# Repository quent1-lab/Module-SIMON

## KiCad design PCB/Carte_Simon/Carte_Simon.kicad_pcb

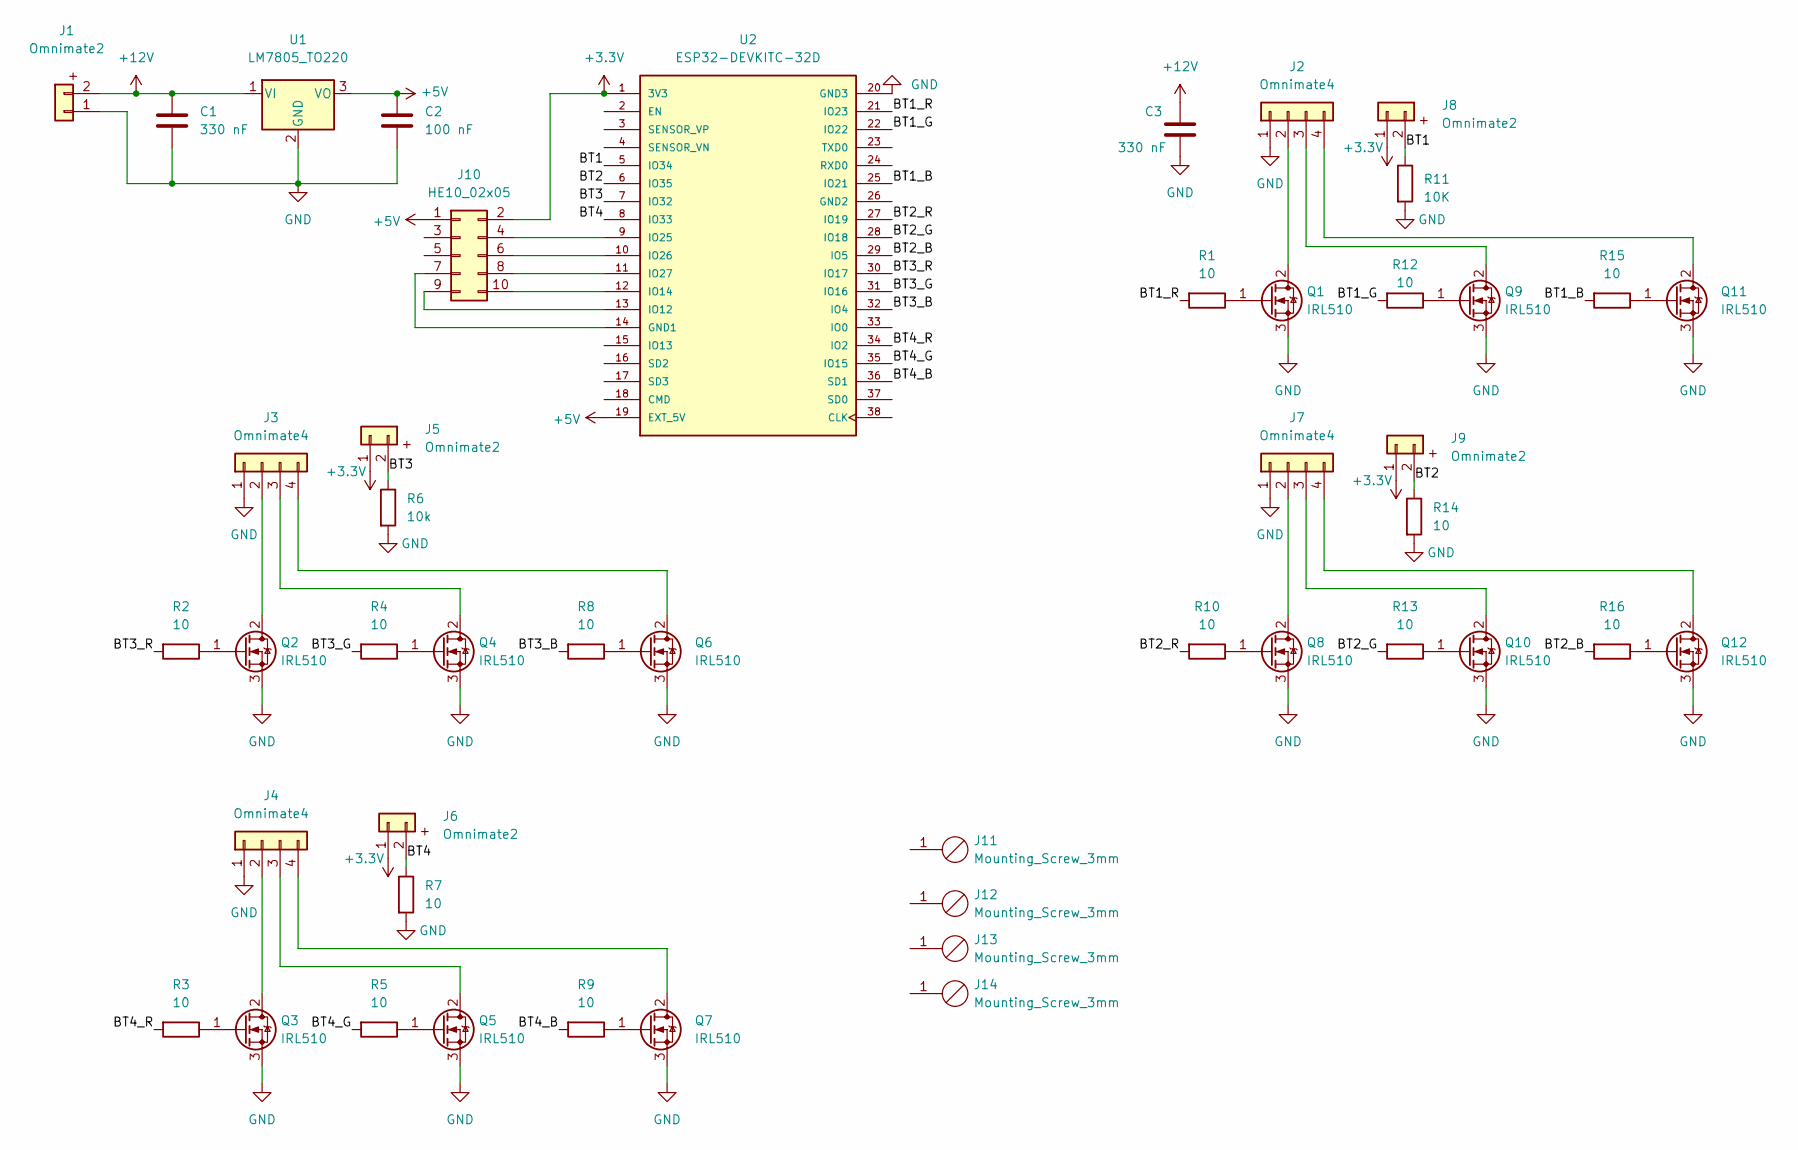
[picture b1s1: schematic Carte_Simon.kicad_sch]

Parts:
C1, C3: 330 nF; C_Rect_L7.0mm_W2.5mm_P5.00mm
C2: 100 nF; C_Rect_L7.0mm_W2.5mm_P5.00mm
J1, J5, J6, J8, J9: Omnimate2; OmnimateSL-5,08_1x02_P5.08mm_Vertical
J2, J3, J4, J7: Omnimate4; OmnimateSL-5,08_1x04_P5.08mm_Vertical
J10: HE10_02x05; HE10_2x05_P2.54mm
J11, J12, J13, J14: Mounting_Screw_3mm
Q1, Q2, Q3, Q4, Q5, Q6, Q7, Q8, Q9, Q10, Q11, Q12: IRL510; TO-220-3_Vertical
R1, R2, R3, R4, R5, R7, R8, R9, R10, R12, R13, R14, R15, R16: 10; R_Axial_DIN0207_L6.3mm_D2.5mm_P10.16mm_Horizontal
R6: 10k; R_Axial_DIN0207_L6.3mm_D2.5mm_P10.16mm_Horizontal
R11: 10K; R_Axial_DIN0207_L6.3mm_D2.5mm_P10.16mm_Horizontal
U1: LM7805_TO220; TO-220-3_Vertical
U2: ESP32-DEVKITC-32D; MODULE_ESP32-DEVKITC-32D; PARTREV 4

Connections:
+3.3V: J5.1, J6.1, J8.1, J9.1, J10.2, U2.1 (3V3)
+5V: C2.1, J10.1, U1.3 (VO), U2.19 (EXT_5V)
+12V: C1.1, C3.1, J1.2, U1.1 (VI)
/BT1: J8.2, R11.1, U2.5 (IO34)
/BT1_B: R15.2, U2.25 (IO21)
/BT1_G: R12.2, U2.22 (IO22)
/BT1_R: R1.2, U2.21 (IO23)
/BT2: J9.2, R14.1, U2.6 (IO35)
/BT2_B: R16.2, U2.29 (IO5)
/BT2_G: R13.2, U2.28 (IO18)
/BT2_R: R10.2, U2.27 (IO19)
/BT3: J5.2, R6.1, U2.7 (IO32)
/BT3_B: R8.2, U2.32 (IO4)
/BT3_G: R4.2, U2.31 (IO16)
/BT3_R: R2.2, U2.30 (IO17)
/BT4: J6.2, R7.1, U2.8 (IO33)
/BT4_B: R9.2, U2.36 (SD1)
/BT4_G: R5.2, U2.35 (IO15)
/BT4_R: R3.2, U2.34 (IO2)
GND: C1.2, C2.2, C3.2, J1.1, J2.1, J3.1, J4.1, J7.1, Q1.3 (S), Q2.3 (S), Q3.3 (S), Q4.3 (S), Q5.3 (S), Q6.3 (S), Q7.3 (S), Q8.3 (S), Q9.3 (S), Q10.3 (S), Q11.3 (S), Q12.3 (S), R6.2, R7.2, R11.2, R14.2, U1.2 (GND), U2.20 (GND3)
unnamed: J2.2, Q1.2 (D)
unnamed: J2.3, Q9.2 (D)
unnamed: J2.4, Q11.2 (D)
unnamed: J3.2, Q2.2 (D)
unnamed: J3.3, Q4.2 (D)
unnamed: J3.4, Q6.2 (D)
unnamed: J4.2, Q3.2 (D)
unnamed: J4.3, Q5.2 (D)
unnamed: J4.4, Q7.2 (D)
unnamed: J7.2, Q8.2 (D)
unnamed: J7.3, Q10.2 (D)
unnamed: J7.4, Q12.2 (D)
unnamed: J10.4, U2.9 (IO25)
unnamed: J10.6, U2.10 (IO26)
unnamed: J10.7, U2.14 (GND1)
unnamed: J10.8, U2.11 (IO27)
unnamed: J10.9, U2.13 (IO12)
unnamed: J10.10, U2.12 (IO14)
unnamed: Q1.1 (G), R1.1
unnamed: Q2.1 (G), R2.1
unnamed: Q3.1 (G), R3.1
unnamed: Q4.1 (G), R4.1
unnamed: Q5.1 (G), R5.1
unnamed: Q6.1 (G), R8.1
unnamed: Q7.1 (G), R9.1
unnamed: Q8.1 (G), R10.1
unnamed: Q9.1 (G), R12.1
unnamed: Q10.1 (G), R13.1
unnamed: Q11.1 (G), R15.1
unnamed: Q12.1 (G), R16.1

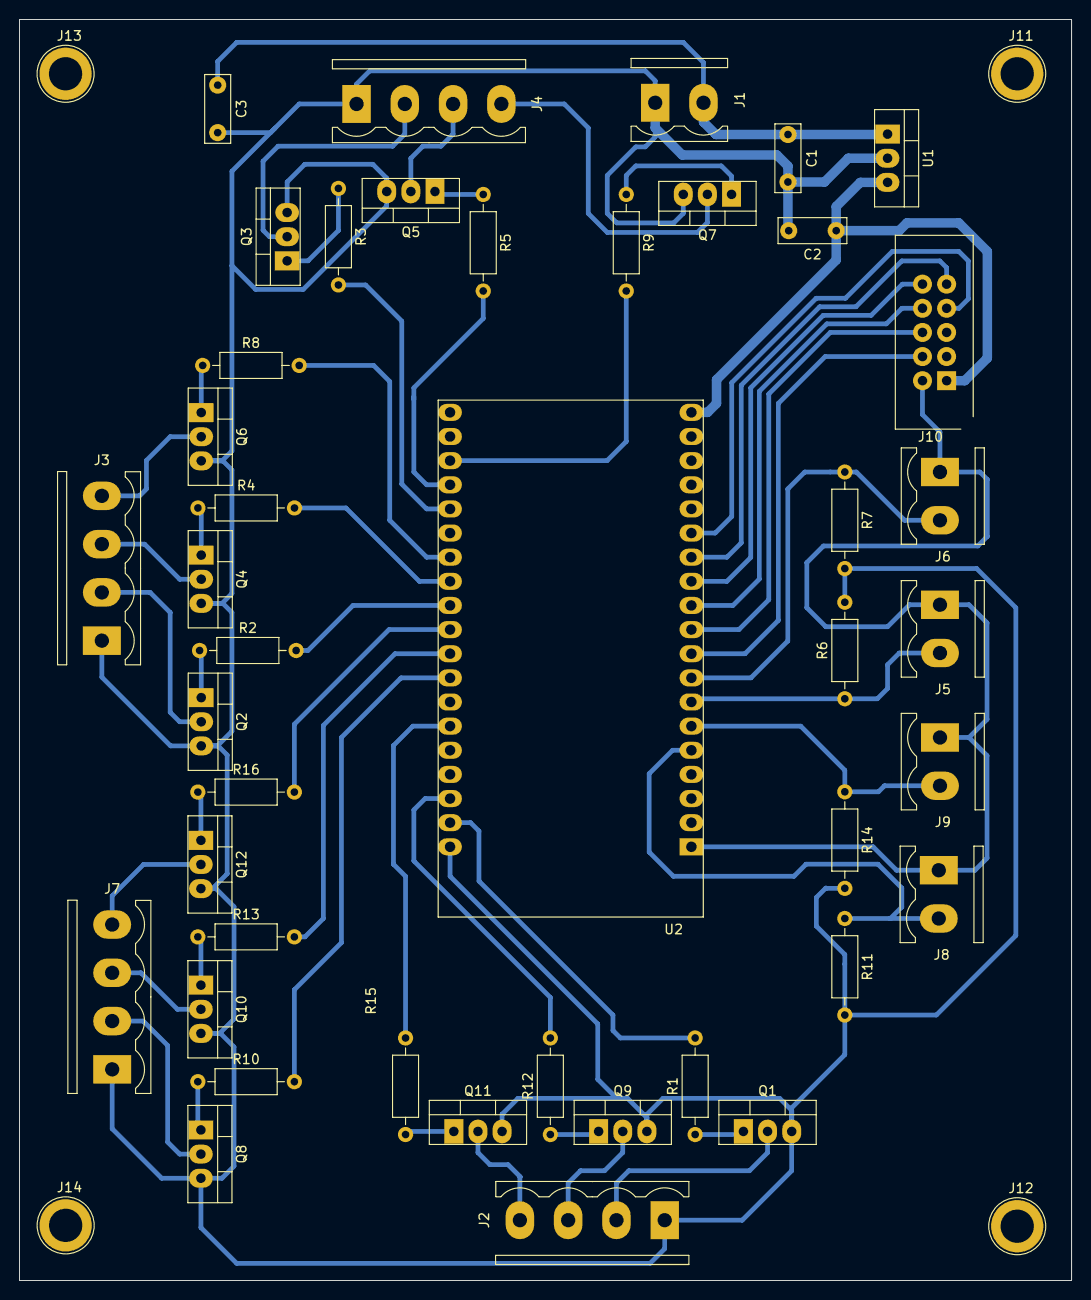
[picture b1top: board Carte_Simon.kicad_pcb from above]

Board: 2 copper layers, 110.7 x 132.7 mm, 47 parts (0 on the bottom side), 50 nets.

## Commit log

2023-02-01 V1_SIMON
2023-02-02 Band_d'essais
2023-02-02 TEST_BOARD
2023-02-06 TEST_BOARD_V1.2
2023-02-06 SIMON_V1.1
2023-02-07 SIMON_V1.2
2023-02-15 SIMON_V2.0 (wifi)
2023-02-15 Add lcd function
2023-02-20 translate the code into english
2023-03-10 Add PCB and new buttons
2023-03-10 Add lib Bouton
2023-03-11 Add setup led
2023-03-11 Add algo led random place
2023-03-11 Add function led_PWM
2023-03-12 fix variable and add function test PWM
2023-03-12 Add function led PWM off and fix error
2023-03-12 Add function rainbow
2023-03-15 Add Function send json
2023-03-25 Add carte bouton
2023-04-03 fix function test
2023-04-03 modify function test
2023-04-05 fix bug and V2 Simon
2023-04-07 fix bug in game
2023-05-02 change the name of the functions of the library
2023-05-20 Add 2 3 truc
2023-06-21 remove server web
2023-06-22 espnow first start
2023-06-22 espnow run
2023-06-27 Vfinale 1.2
2024-02-28 Mise à jour des broches et des niveaux de jeu
